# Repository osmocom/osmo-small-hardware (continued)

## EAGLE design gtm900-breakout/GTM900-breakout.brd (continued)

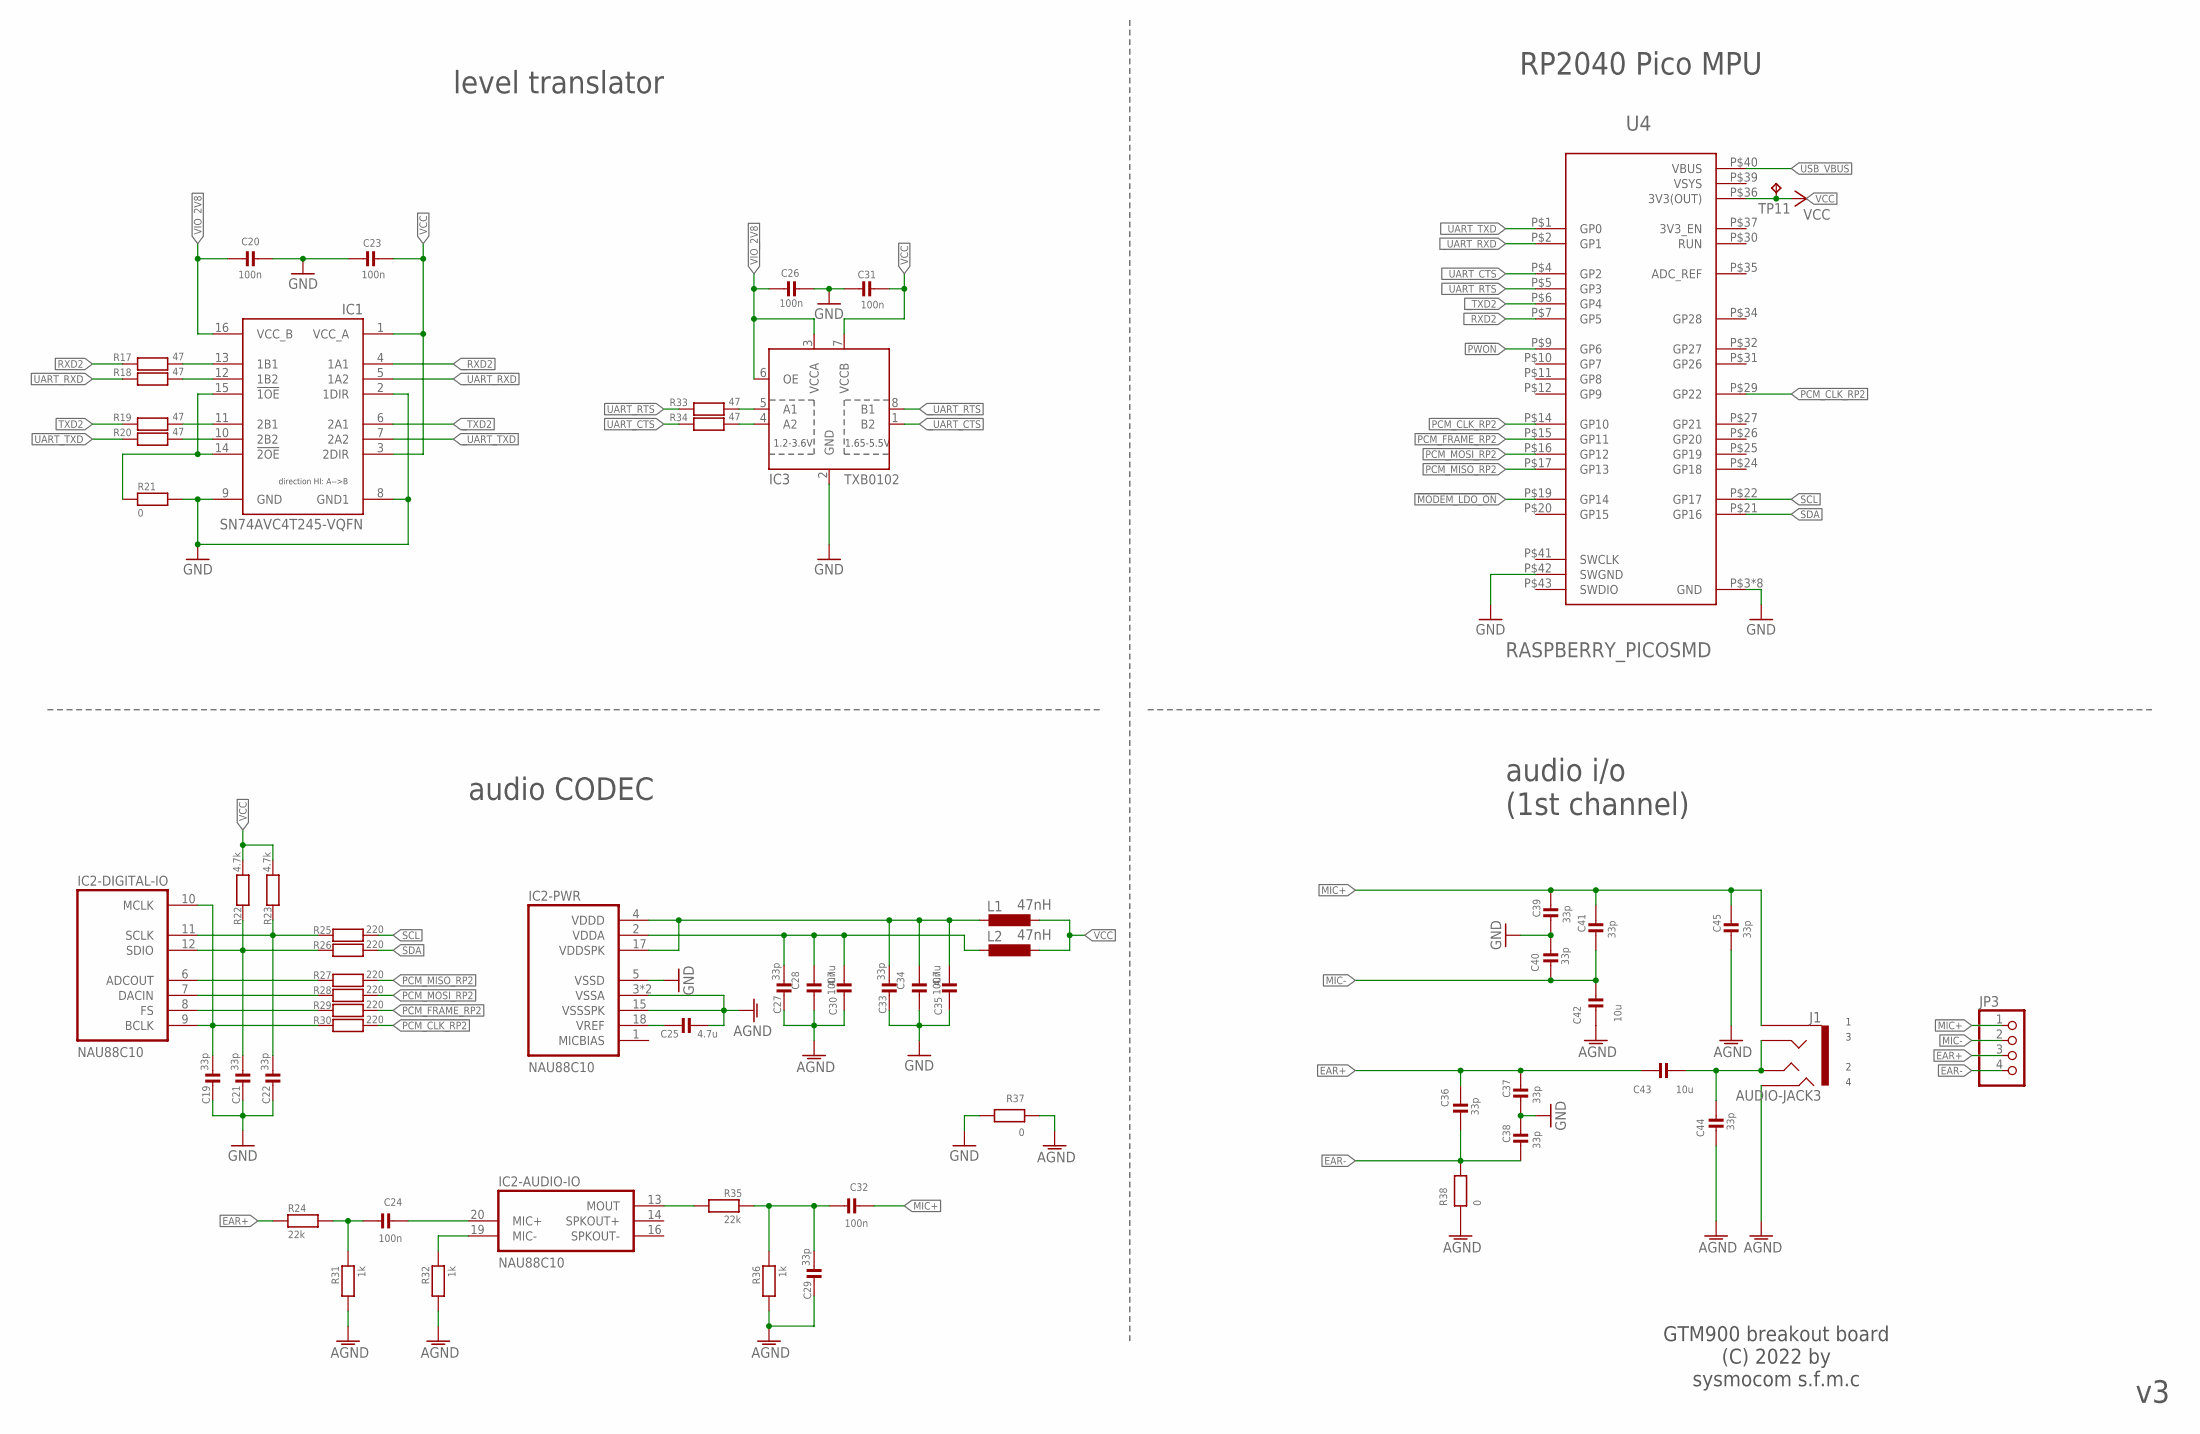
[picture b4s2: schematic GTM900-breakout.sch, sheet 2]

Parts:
C19, C21, C22, C27, C29, C33, C36, C37, C38, C39, C40, C41, C44, C45: 33p; _0402; MANUFACTURERPARTNUMBER CL05C330JB5NNNC; LCSC_PART C70465
C20, C23, C24, C26, C28, C31, C32, C34: 100n; _0603; MANUFACTURERPARTNUMBER CL10B104KB8NNWC; LCSC_PART C14663
C25, C30, C35: 4.7u; _0603; MANUFACTURERPARTNUMBER CC0603KRX5R6BB475; LCSC_PART C109456
C42, C43: 10u; _0805; MANUFACTURERPARTNUMBER GRM21BR61C106KE15K; LCSC_PART C408141
IC1: SN74AVC4T245-VQFN; VQFN-N16; MANUFACTURERPARTNUMBER SN74AVC4T245RGYR; LCSC_PART C2872438
IC2: NAU88C10; QFN20; MANUFACTURERPARTNUMBER NAU88C10YG; LCSC_PART C914208
IC3: TXB0102; VSSOP-8; MANUFACTURERPARTNUMBER TXB0102DCUR; LCSC_PART C60709
J1: AUDIO-JACK3; AUDIO-JACK-TRRS-SMD; MANUFACTURERPARTNUMBER SJ2-3574A-SMT-TR; LCSC_PART C4991637
JP3: HEADER-1X476MIL; 1X04_ROUND_76; MANUFACTURERPARTNUMBER UNKNOWN MANUFACTURER PART NUMBER; LCSC_PART UNKNOWN LCSC_PART
L1, L2: 47nH; _0603; MANUFACTURERPARTNUMBER BSCH0016080847NJ00; LCSC_PART C6135425
R17, R18, R19, R20, R33, R34: 47; _0603; MANUFACTURERPARTNUMBER RC0603JR-0747RL; LCSC_PART C114623
R21, R37, R38: 0; _0603; MANUFACTURERPARTNUMBER UNKNOWN MANUFACTURER PART NUMBER; LCSC_PART C136582
R22, R23: 4.7k; _0603; MANUFACTURERPARTNUMBER RC0603JR-074K7L; LCSC_PART C105428
R24, R35: 22k; _0603; MANUFACTURERPARTNUMBER RC0603FR-0722KL; LCSC_PART C114065
R25, R26, R27, R28, R29, R30: 220; _0603; MANUFACTURERPARTNUMBER RC0603FR-07220RL; LCSC_PART C107696
R31, R32, R36: 1k; _0603; MANUFACTURERPARTNUMBER RR0816P-102-D; LCSC_PART C116692
TP11: TPTP10R; TP10R; MANUFACTURERPARTNUMBER UNKNOWN MANUFACTURER PART NUMBER; LCSC_PART UNKNOWN LCSC_PART
U4: RASPBERRY_PICOSMD; PICO-PKG-SMD; MANUFACTURERPARTNUMBER SC0915; LCSC_PART UNKNOWN LCSC_PART

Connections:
!MODEM_LDO_ON: U4.P$19 (GP14); also elsewhere on the board
!PWON: U4.P$9 (GP6); also elsewhere on the board
AGND: C25.1, C27.2, C28.2, C29.2, C30.2, C42.2, C44.1, C45.2, IC2.3 (VSSA), IC2.15 (VSSSPK), IC2.EXP (VSSA), J1.4 (RING2), R31.2, R32.2, R36.2, R37.1, R38.1
EAR+: C36.2, C37.1, C43.2, JP3.3, R24.1; also elsewhere on the board
EAR-: C36.1, C38.2, JP3.4, R38.2; also elsewhere on the board
GND: C19.2, C20.2, C21.2, C22.2, C23.1, C26.2, C31.1, C33.2, C34.2, C35.2, C37.2, C38.1, C39.2, C40.2, IC1.2 (1DIR), IC1.8 (GND1), IC1.9 (GND), IC2.5 (VSSD), IC3.2 (GND), R21.2, R37.2, U4.P$3 (GND), U4.P$8 (GND), U4.P$13 (GND), U4.P$18 (GND), U4.P$23 (GND), U4.P$28 (GND), U4.P$33 (GND), U4.P$38 (GND), U4.P$42 (SWGND); also elsewhere on the board
MIC+: C32.1, C39.1, C41.1, C45.1, J1.1 (EARTH), JP3.1; also elsewhere on the board
MIC-: C40.1, C41.2, C42.1, JP3.2; also elsewhere on the board
MICBIAS: IC2.1 (MICBIAS)
unnamed: C24.2, R24.2, R31.1
unnamed: C43.1, C44.2, J1.2 (TIP), J1.3 (RING1)
unnamed: C19.1, IC2.9 (BCLK), IC2.10 (MCLK), R30.1
unnamed: IC2.8 (FS), R29.1
unnamed: IC2.7 (DACIN), R28.1
unnamed: IC2.6 (ADCOUT), R27.1
unnamed: C29.1, C32.2, R35.2, R36.1
unnamed: IC2.19 (MIC-), R32.1
unnamed: C33.1, C34.1, C35.1, IC2.4 (VDDD), IC2.17 (VDDSPK), L1.2
unnamed: IC1.14 (!2OE), IC1.15 (!1OE), R21.1
unnamed: IC1.13 (1B1), R17.1
unnamed: C27.1, C28.1, C30.1, IC2.2 (VDDA), L2.2
unnamed: C21.1, IC2.12 (SDIO), R22.1, R26.1
unnamed: C22.1, IC2.11 (SCLK), R23.1, R25.1
unnamed: IC1.12 (1B2), R18.1
unnamed: C25.2, IC2.18 (VREF)
unnamed: IC1.11 (2B1), R19.1
unnamed: IC2.13 (MOUT), R35.1
unnamed: C24.1, IC2.20 (MIC+)
unnamed: IC1.10 (2B2), R20.1
unnamed: IC3.5 (A1), R33.1
unnamed: IC3.4 (A2), R34.1
PCM_CLK_RP2: R30.2, U4.P$14 (GP10), U4.P$29 (GP22)
PCM_FRAME_RP2: R29.2, U4.P$15 (GP11)
PCM_MISO_RP2: R27.2, U4.P$17 (GP13)
PCM_MOSI_RP2: R28.2, U4.P$16 (GP12)
RXD2: R17.2; also elsewhere on the board
SCL: R25.2, U4.P$22 (GP17)
SDA: R26.2, U4.P$21 (GP16)
TXD2: R19.2; also elsewhere on the board
UART_CTS: R34.2; also elsewhere on the board
UART_RTS: R33.2; also elsewhere on the board
UART_RXD: R18.2; also elsewhere on the board
UART_TXD: R20.2; also elsewhere on the board
USB_VBUS: U4.P$40 (VBUS); also elsewhere on the board
VCC: C23.2, C31.2, IC1.1 (VCC_A), IC1.3 (2DIR), IC3.7 (VCCB), L1.1, L2.1, R22.2, R23.2, TP11.TP, U4.P$36 (3V3(OUT))
VIO_2V8: C20.1, C26.1, IC1.16 (VCC_B), IC3.3 (VCCA), IC3.6 (OE); also elsewhere on the board
VSYS: U4.P$39 (VSYS)
_RXD2: IC1.4 (1A1), U4.P$7 (GP5)
_TXD2: IC1.6 (2A1), U4.P$6 (GP4)
_UART_CTS: IC3.1 (B2), U4.P$4 (GP2)
_UART_RTS: IC3.8 (B1), U4.P$5 (GP3)
_UART_RXD: IC1.5 (1A2), U4.P$2 (GP1)
_UART_TXD: IC1.7 (2A2), U4.P$1 (GP0)

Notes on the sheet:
audio i/o (1st channel)
GTM900 breakout board (C) 2022 by sysmocom s.f.m.c
level translator
audio CODEC
RP2040 Pico MPU

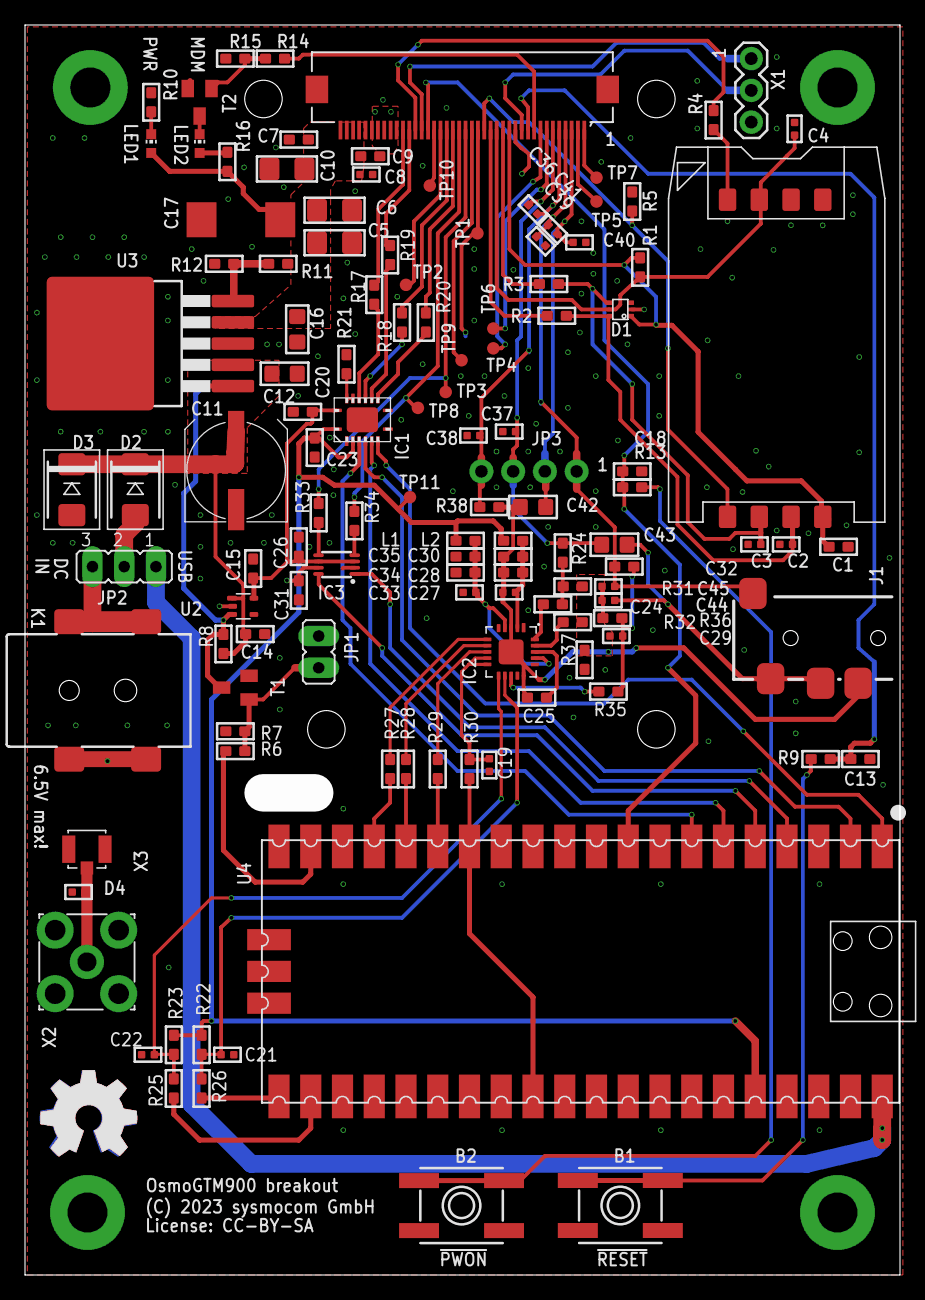
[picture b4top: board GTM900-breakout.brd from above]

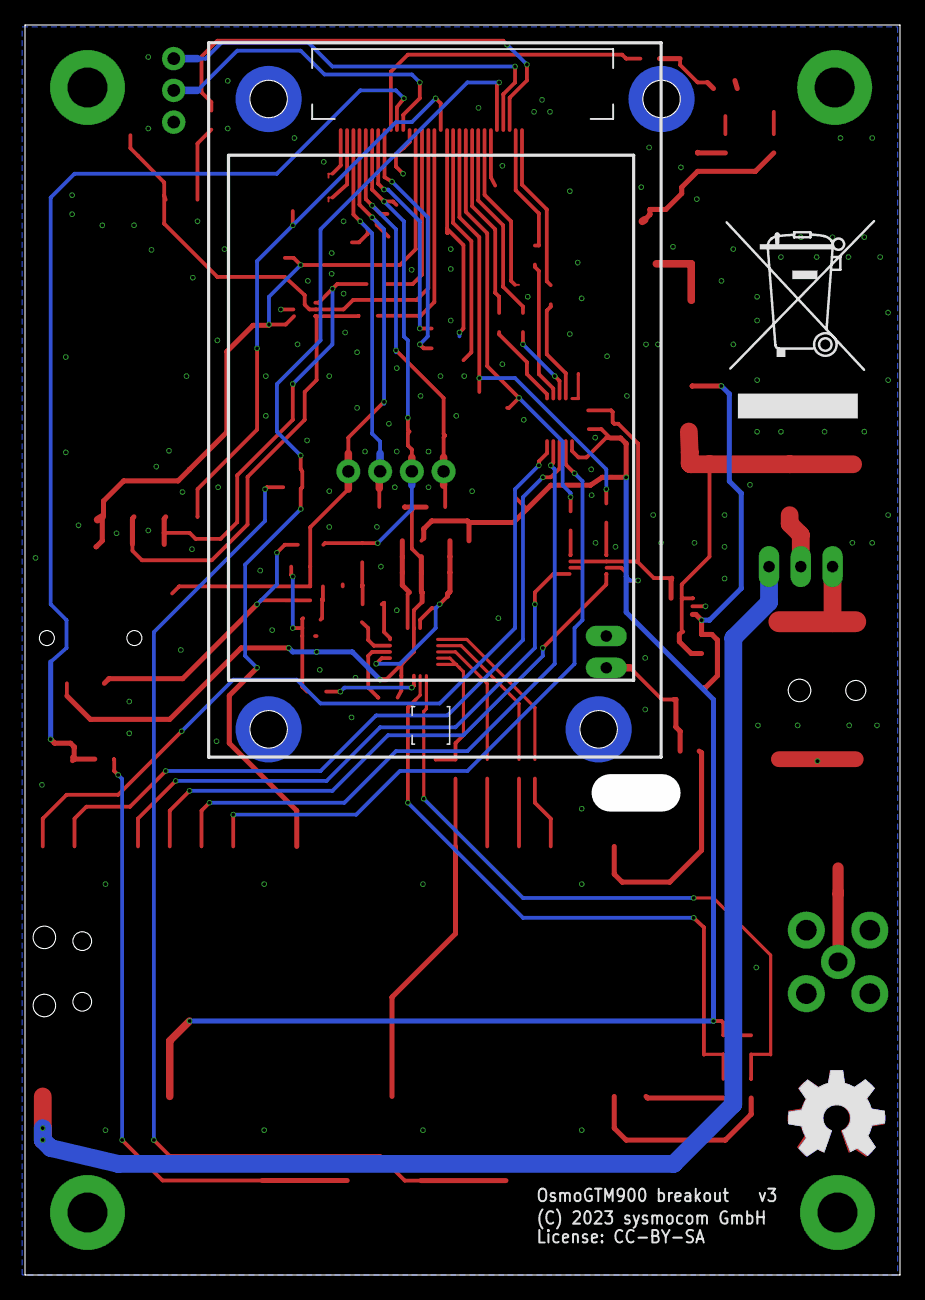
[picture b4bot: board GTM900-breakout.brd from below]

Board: 2 copper layers, 70.0 x 100.0 mm, 126 parts (3 on the bottom side), 86 nets.

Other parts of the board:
U$1, U$3: OSHW_8MM_COPPER
U$2: WEEE_BIN

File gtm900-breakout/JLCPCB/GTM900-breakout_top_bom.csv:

Comment,Designator,Footprint,"LCSC Part #"
uFL,X3,HRS_UFL,C434812
"0R jumper","R21 R37 R38",_0603,C136582
1k,"R9 R13 R31 R32 R36",_0603,C116692
1u,"C14 C15",_0603,C1592
4.7k,"R4 R8 R22 R23",_0603,C105428
4.7u,"C25 C30 C35",_0603,C109456
10p,C9,_0603,C106245
10u,"C12 C16 C42 C43",_0805,C408141
15k,R1,_0603,C114661
22k,"R6 R7 R12 R14 R15 R24 R35",_0603,C114065
33p,"C2 C3 C4 C8 C19 C21 C22 C27 C29 C33 C36 C37 C38 C39 C40 C41 C44 C45",_0402,C70465
47R,"R2 R3 R17 R18 R19 R20 R33 R34",_0603,C114623
47k,R5,_0603,C105579
47nH,"L1 L2",_0603,C6135425
100n,"C1 C7 C13 C18 C20 C23 C24 C26 C28 C31 C32 C34",_0603,C141084
100u,"C5 C6 C10",1206,C15008
200k,R11,_0603,C105574
220R,"R25 R26 R27 R28 R29 R30",_0603,C107696
330R,"R10 R16",_0603,C105879
470u,C11,UD-8X10_NICHICON,C445244
ACDBB540-HF,D2,SMBDIODE,C3019736
AUDIO-JACK3,J1,AUDIO-JACK-TRRS-SMD,C4991637
BC847,"T1 T2",SOT23-BEC,C8664
EVQQ2K03W,"B1 B2",EVQ-Q2,C713484
FH12A-40S-0.5SH(55),U1,HIROSE_FH12A-40S-0.5SH(55),C506795
GG040205170N2P,D4,_0402,C597648
GREEN,LED1,CHIP-LED0603,C5554150
MCP1827T-ADJE/ET,U3,TI_KTT_DPAK2,C152196
MIC5366,U2,SC70-5,C626107
NAU88C10,IC2,QFN20,C914208
PESD5V0UBV,D1,SOT666,C552582
PJ-002BH-SMT-TR,K1,694108106102,C3094235
SIM-105B-ARP8,SIM1,SIM-105B-ARP8,C920196
SMBJP6KE6.8A-TP,D3,SMBDIODE,C725414
SN74AVC4T245-VQFN,IC1,VQFN-N16,C2872438
TXB0102,IC3,VSSOP-8,C60709
YELLOW,LED2,CHIP-LED0603,C5875726

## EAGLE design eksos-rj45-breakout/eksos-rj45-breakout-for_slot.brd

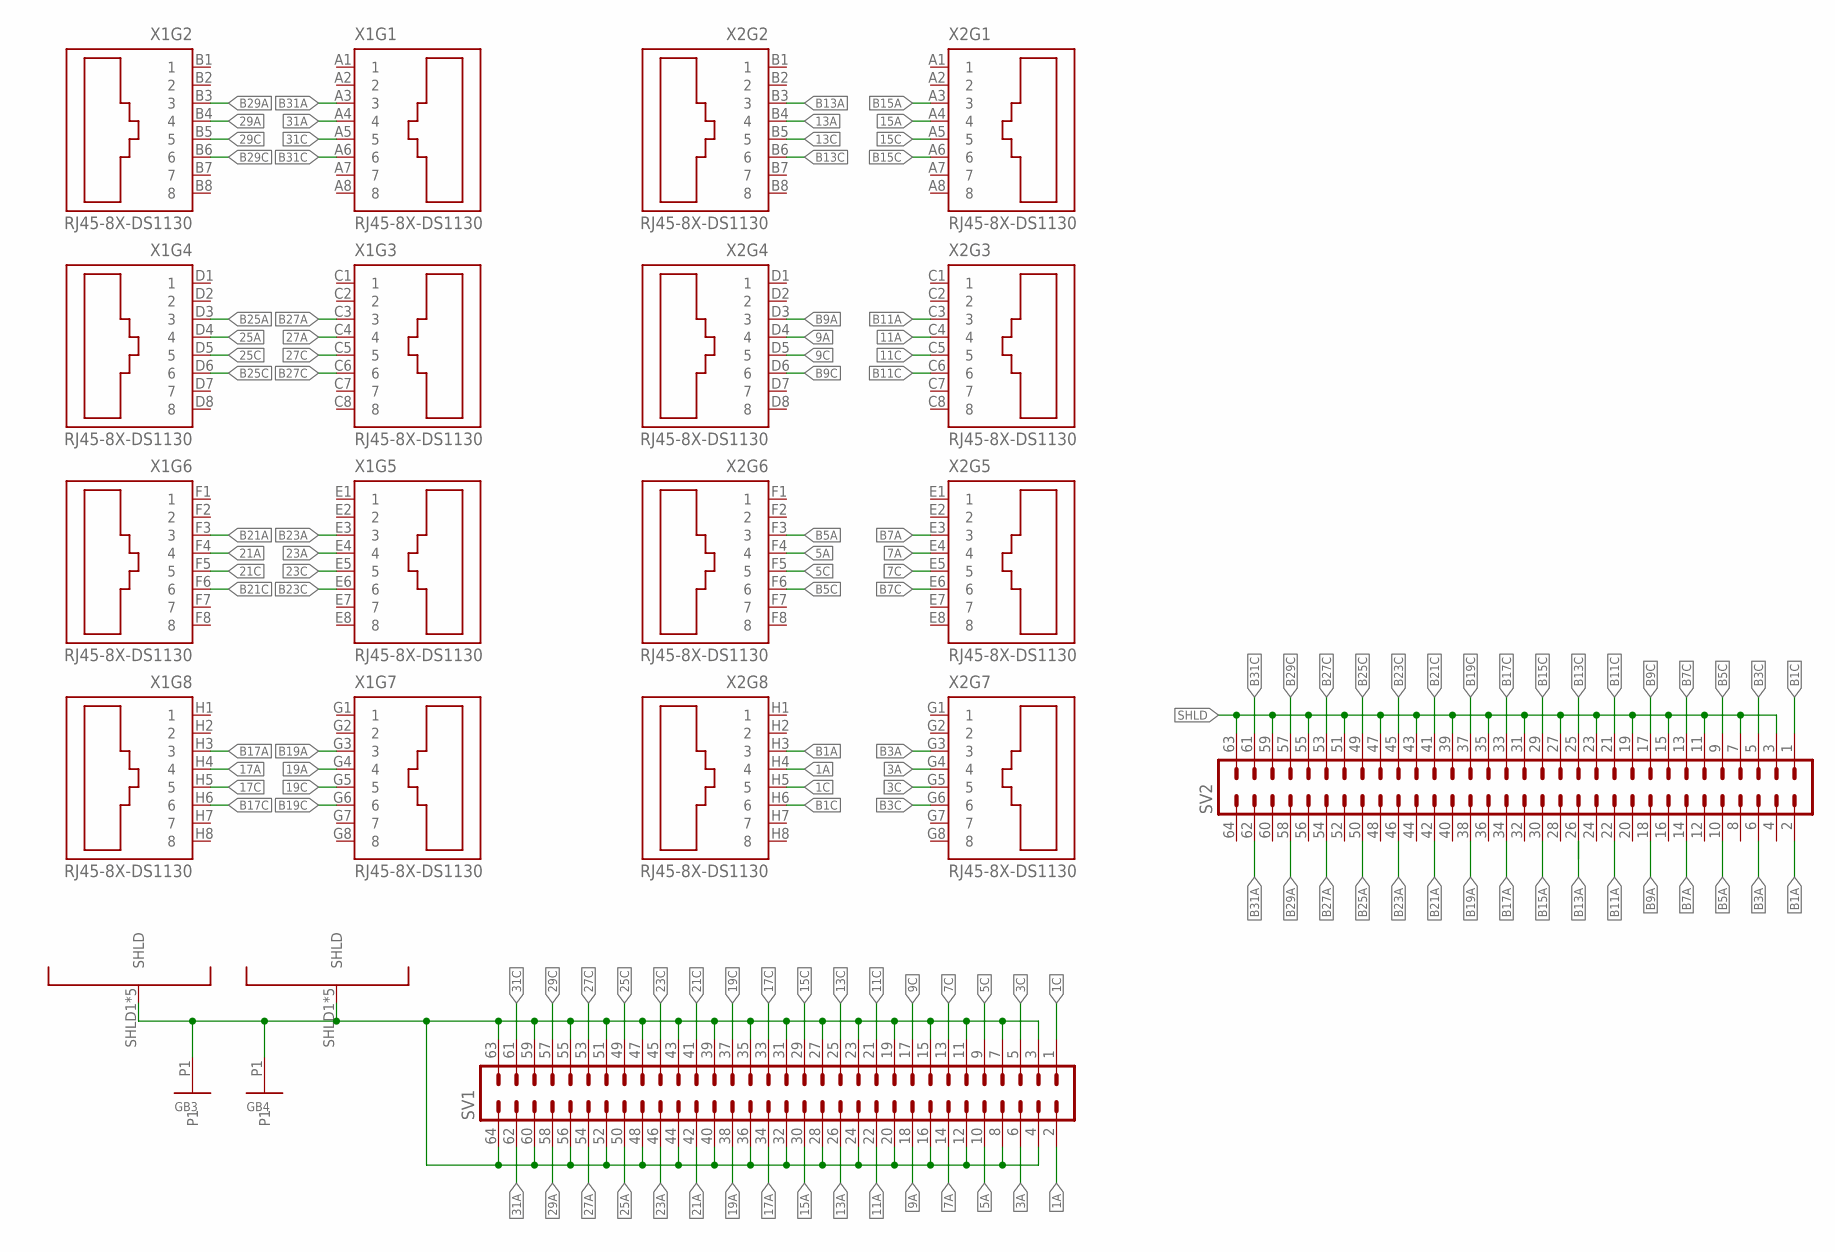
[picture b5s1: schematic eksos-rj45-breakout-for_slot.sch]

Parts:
GB3, GB4: GEWINDEBLOCK-6X6X12M3; GB6X6X12_VIA
SV1, SV2: ML64
X1, X2: RJ45-8X-DS1130; DS1130

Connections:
1A: SV1.2, X2.H4 (4)
1C: SV1.1, X2.H5 (5)
3A: SV1.6, X2.G4 (4)
3C: SV1.5, X2.G5 (5)
5A: SV1.10, X2.F4 (4)
5C: SV1.9, X2.F5 (5)
7A: SV1.14, X2.E4 (4)
7C: SV1.13, X2.E5 (5)
9A: SV1.18, X2.D4 (4)
9C: SV1.17, X2.D5 (5)
11A: SV1.22, X2.C4 (4)
11C: SV1.21, X2.C5 (5)
13A: SV1.26, X2.B4 (4)
13C: SV1.25, X2.B5 (5)
15A: SV1.30, X2.A4 (4)
15C: SV1.29, X2.A5 (5)
17A: SV1.34, X1.H4 (4)
17C: SV1.33, X1.H5 (5)
19A: SV1.38, X1.G4 (4)
19C: SV1.37, X1.G5 (5)
21A: SV1.42, X1.F4 (4)
21C: SV1.41, X1.F5 (5)
23A: SV1.46, X1.E4 (4)
23C: SV1.45, X1.E5 (5)
25A: SV1.50, X1.D4 (4)
25C: SV1.49, X1.D5 (5)
27A: SV1.54, X1.C4 (4)
27C: SV1.53, X1.C5 (5)
29A: SV1.58, X1.B4 (4)
29C: SV1.57, X1.B5 (5)
31A: SV1.62, X1.A4 (4)
31C: SV1.61, X1.A5 (5)
B1A: SV2.2, X2.H3 (3)
B1C: SV2.1, X2.H6 (6)
B3A: SV2.6, X2.G3 (3)
B3C: SV2.5, X2.G6 (6)
B5A: SV2.10, X2.F3 (3)
B5C: SV2.9, X2.F6 (6)
B7A: SV2.14, X2.E3 (3)
B7C: SV2.13, X2.E6 (6)
B9A: SV2.18, X2.D3 (3)
B9C: SV2.17, X2.D6 (6)
B11A: SV2.22, X2.C3 (3)
B11C: SV2.21, X2.C6 (6)
B13A: SV2.26, X2.B3 (3)
B13C: SV2.25, X2.B6 (6)
B15A: SV2.30, X2.A3 (3)
B15C: SV2.29, X2.A6 (6)
B17A: SV2.34, X1.H3 (3)
B17C: SV2.33, X1.H6 (6)
B19A: SV2.38, X1.G3 (3)
B19C: SV2.37, X1.G6 (6)
B21A: SV2.42, X1.F3 (3)
B21C: SV2.41, X1.F6 (6)
B23A: SV2.46, X1.E3 (3)
B23C: SV2.45, X1.E6 (6)
B25A: SV2.50, X1.D3 (3)
B25C: SV2.49, X1.D6 (6)
B27A: SV2.54, X1.C3 (3)
B27C: SV2.53, X1.C6 (6)
B29A: SV2.58, X1.B3 (3)
B29C: SV2.57, X1.B6 (6)
B31A: SV2.62, X1.A3 (3)
B31C: SV2.61, X1.A6 (6)
SHLD: GB3.P1, GB4.P1, SV1.3, SV1.4, SV1.7, SV1.8, SV1.11, SV1.12, SV1.15, SV1.16, SV1.19, SV1.20, SV1.23, SV1.24, SV1.27, SV1.28, SV1.31, SV1.32, SV1.35, SV1.36, SV1.39, SV1.40, SV1.43, SV1.44, SV1.47, SV1.48, SV1.51, SV1.52, SV1.55, SV1.56, SV1.59, SV1.60, SV1.63, SV1.64, SV2.3, SV2.7, SV2.11, SV2.15, SV2.19, SV2.23, SV2.27, SV2.31, SV2.35, SV2.39, SV2.43, SV2.47, SV2.51, SV2.55, SV2.59, SV2.63, X1.SHLD1 (SHLD), X1.SHLD2 (SHLD), X1.SHLD3 (SHLD), X1.SHLD4 (SHLD), X1.SHLD5 (SHLD), X2.SHLD1 (SHLD), X2.SHLD2 (SHLD), X2.SHLD3 (SHLD), X2.SHLD4 (SHLD), X2.SHLD5 (SHLD)

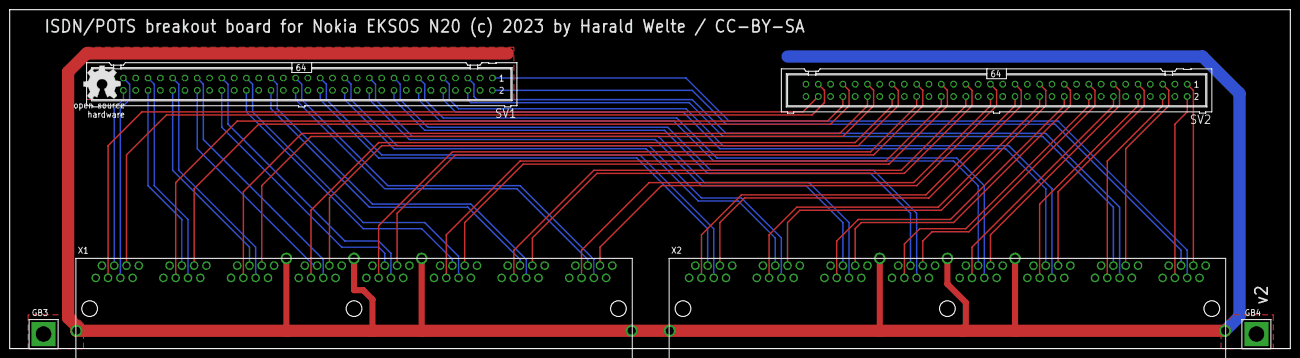
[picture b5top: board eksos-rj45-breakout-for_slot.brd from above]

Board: 2 copper layers, 264.5 x 70.0 mm, 7 parts (0 on the bottom side), 65 nets.

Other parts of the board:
U$1: OSHW_8MM

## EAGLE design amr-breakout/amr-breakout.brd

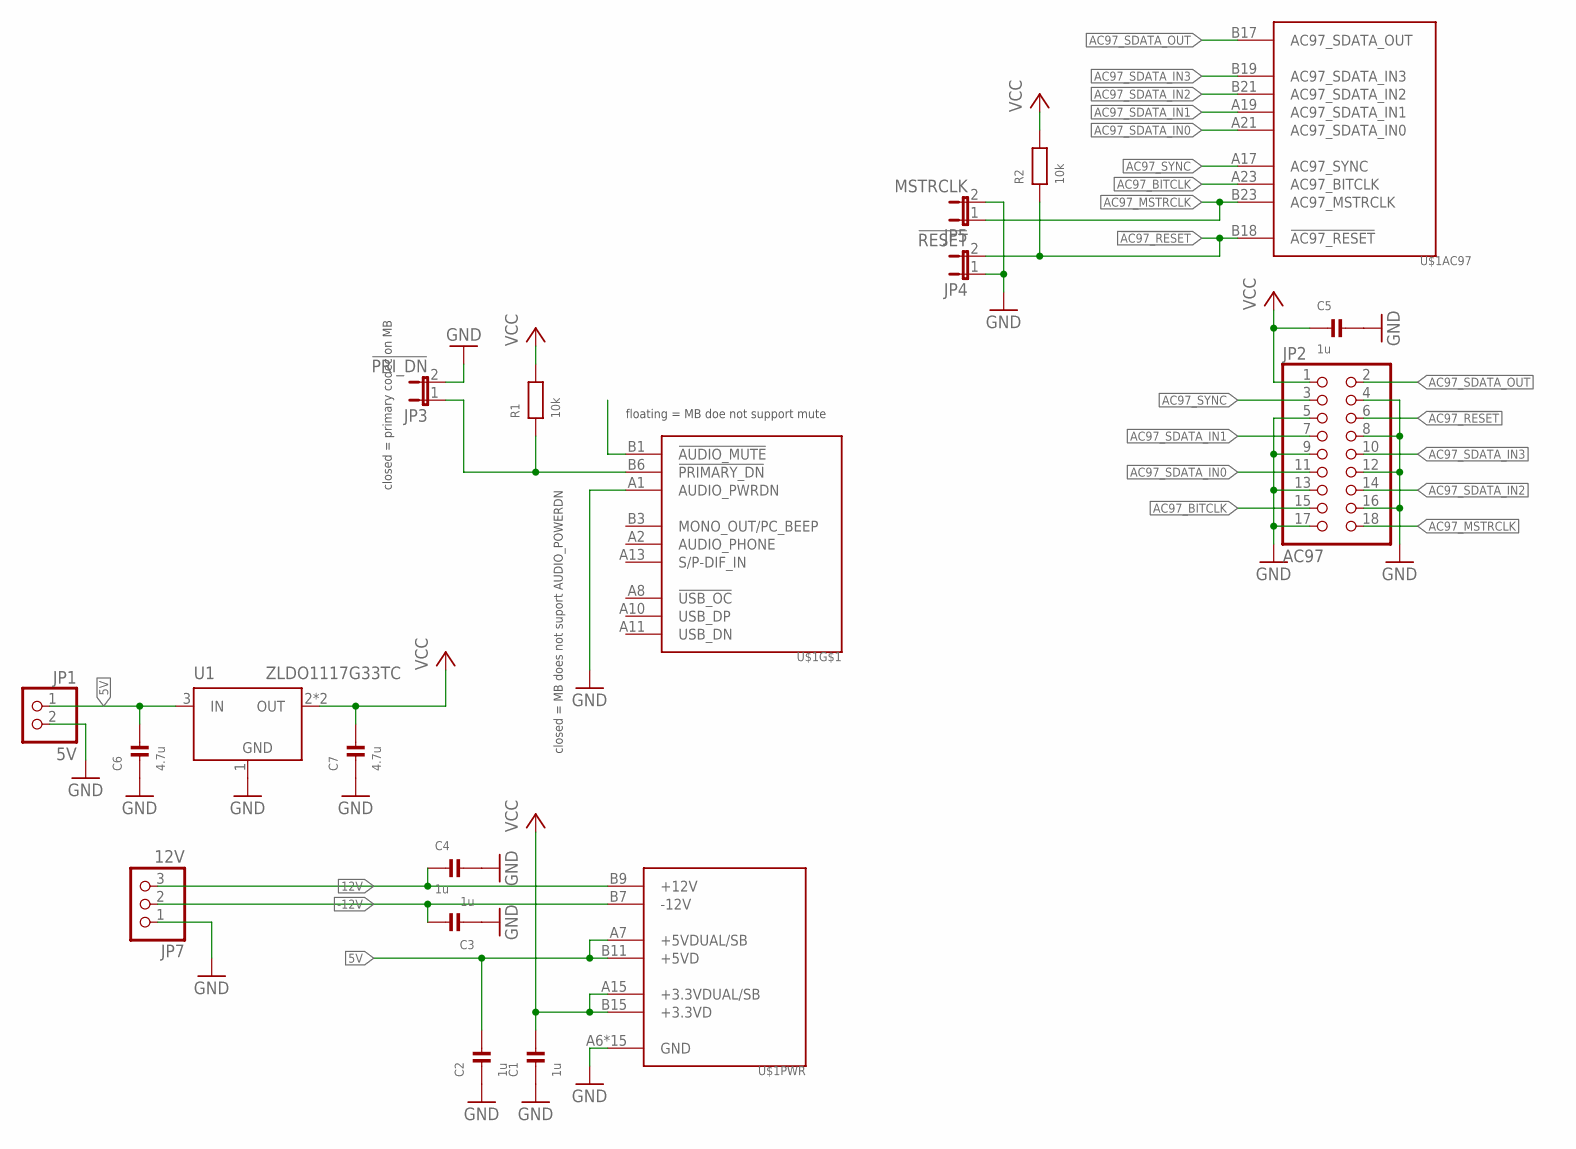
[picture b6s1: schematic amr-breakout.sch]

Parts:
C1, C2, C3, C4, C5: 1u; _0603
C6, C7: 4.7u; _0805
JP1: 5V; 1X02
JP2: AC97; 2X09
JP3: !PRI_DN; JP1
JP4: !RESET; JP1
JP5: MSTRCLK; JP1
JP7: 12V; 1X03
R1, R2: 10k; _0603
U1: ZLDO1117G33TC; SOT223
U$1: AMR-SLOT; 5650090-7

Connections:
5V: C2.2, C6.2, JP1.1, U1.3 (IN), U$1.A7 (+5VDUAL/SB), U$1.B11 (+5VD)
12V: C4.1, JP7.3, U$1.B9 (+12V)
!AC97_RESET: JP2.6, JP4.2, R2.1, U$1.B18 (!AC97_RESET)
!AUDIO_MUTE: U$1.B1 (!AUDIO_MUTE)
!PRIMARY_DN: JP3.1, R1.1, U$1.B6 (!PRIMARY_DN)
-12V: C3.2, JP7.2, U$1.B7 (-12V)
AC97_BITCLK: JP2.15, U$1.A23 (AC97_BITCLK)
AC97_MSTRCLK: JP2.18, JP5.1, U$1.B23 (AC97_MSTRCLK)
AC97_SDATA_IN0: JP2.11, U$1.A21 (AC97_SDATA_IN0)
AC97_SDATA_IN1: JP2.7, U$1.A19 (AC97_SDATA_IN1)
AC97_SDATA_IN2: JP2.14, U$1.B21 (AC97_SDATA_IN2)
AC97_SDATA_IN3: JP2.10, U$1.B19 (AC97_SDATA_IN3)
AC97_SDATA_OUT: JP2.2, U$1.B17 (AC97_SDATA_OUT)
AC97_SYNC: JP2.3, U$1.A17 (AC97_SYNC)
GND: C1.1, C2.1, C3.1, C4.2, C5.2, C6.1, C7.1, JP1.2, JP2.4, JP2.5, JP2.8, JP2.9, JP2.12, JP2.13, JP2.16, JP2.17, JP3.2, JP4.1, JP5.2, JP7.1, U1.1 (GND), U$1.A1 (AUDIO_PWRDN), U$1.A6 (GND), U$1.A9 (GND), U$1.A12 (GND), U$1.A14 (GND), U$1.A16 (GND), U$1.A18 (GND), U$1.A20 (GND), U$1.A22 (GND), U$1.B2 (GND), U$1.B8 (GND), U$1.B10 (GND), U$1.B12 (GND), U$1.B16 (GND), U$1.B20 (GND), U$1.B22 (GND)
VCC: C1.2, C5.1, C7.2, JP2.1, R1.2, R2.2, U1.2 (OUT), U1.4 (OUT), U$1.A15 (+3.3VDUAL/SB), U$1.B15 (+3.3VD)

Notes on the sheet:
closed = MB does not suport AUDIO_POWERDN
floating = MB doe not support mute
closed = primary codec on MB

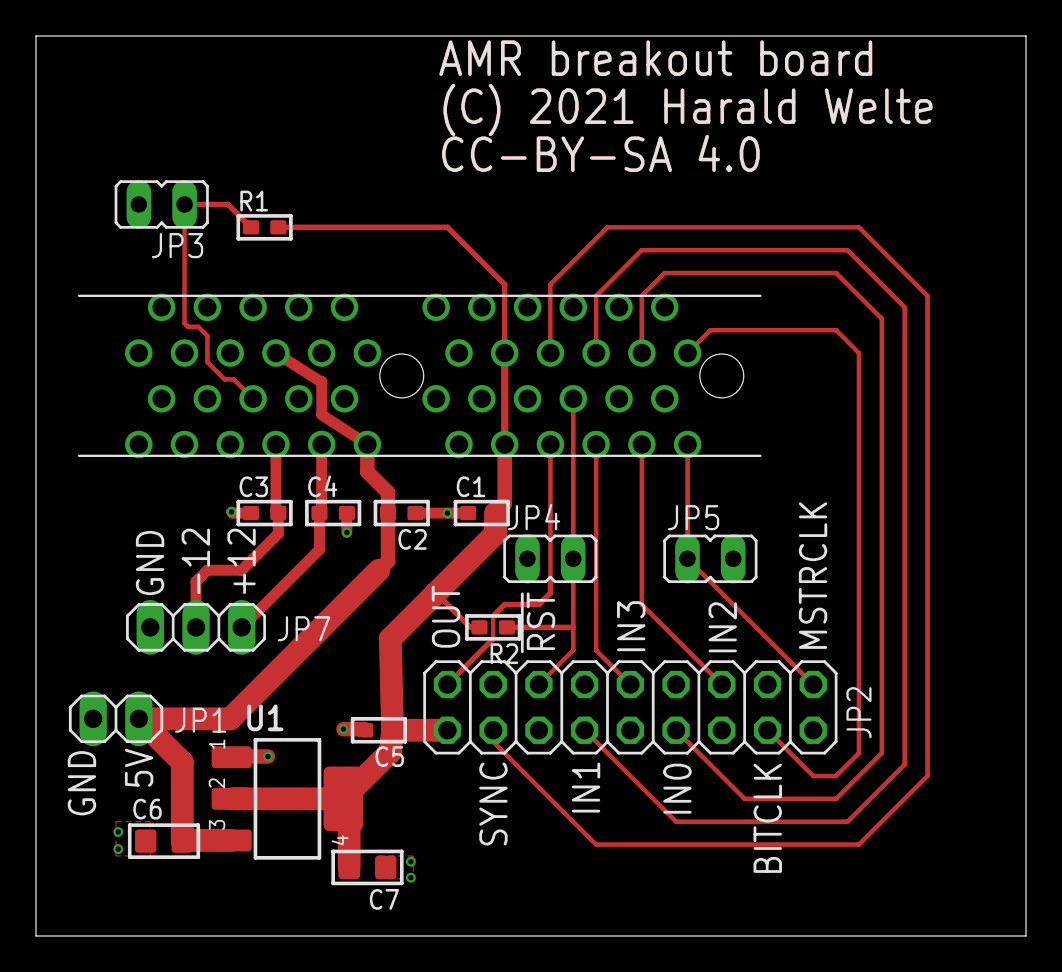
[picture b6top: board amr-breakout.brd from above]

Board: 2 copper layers, 55.0 x 50.0 mm, 17 parts (0 on the bottom side), 15 nets.

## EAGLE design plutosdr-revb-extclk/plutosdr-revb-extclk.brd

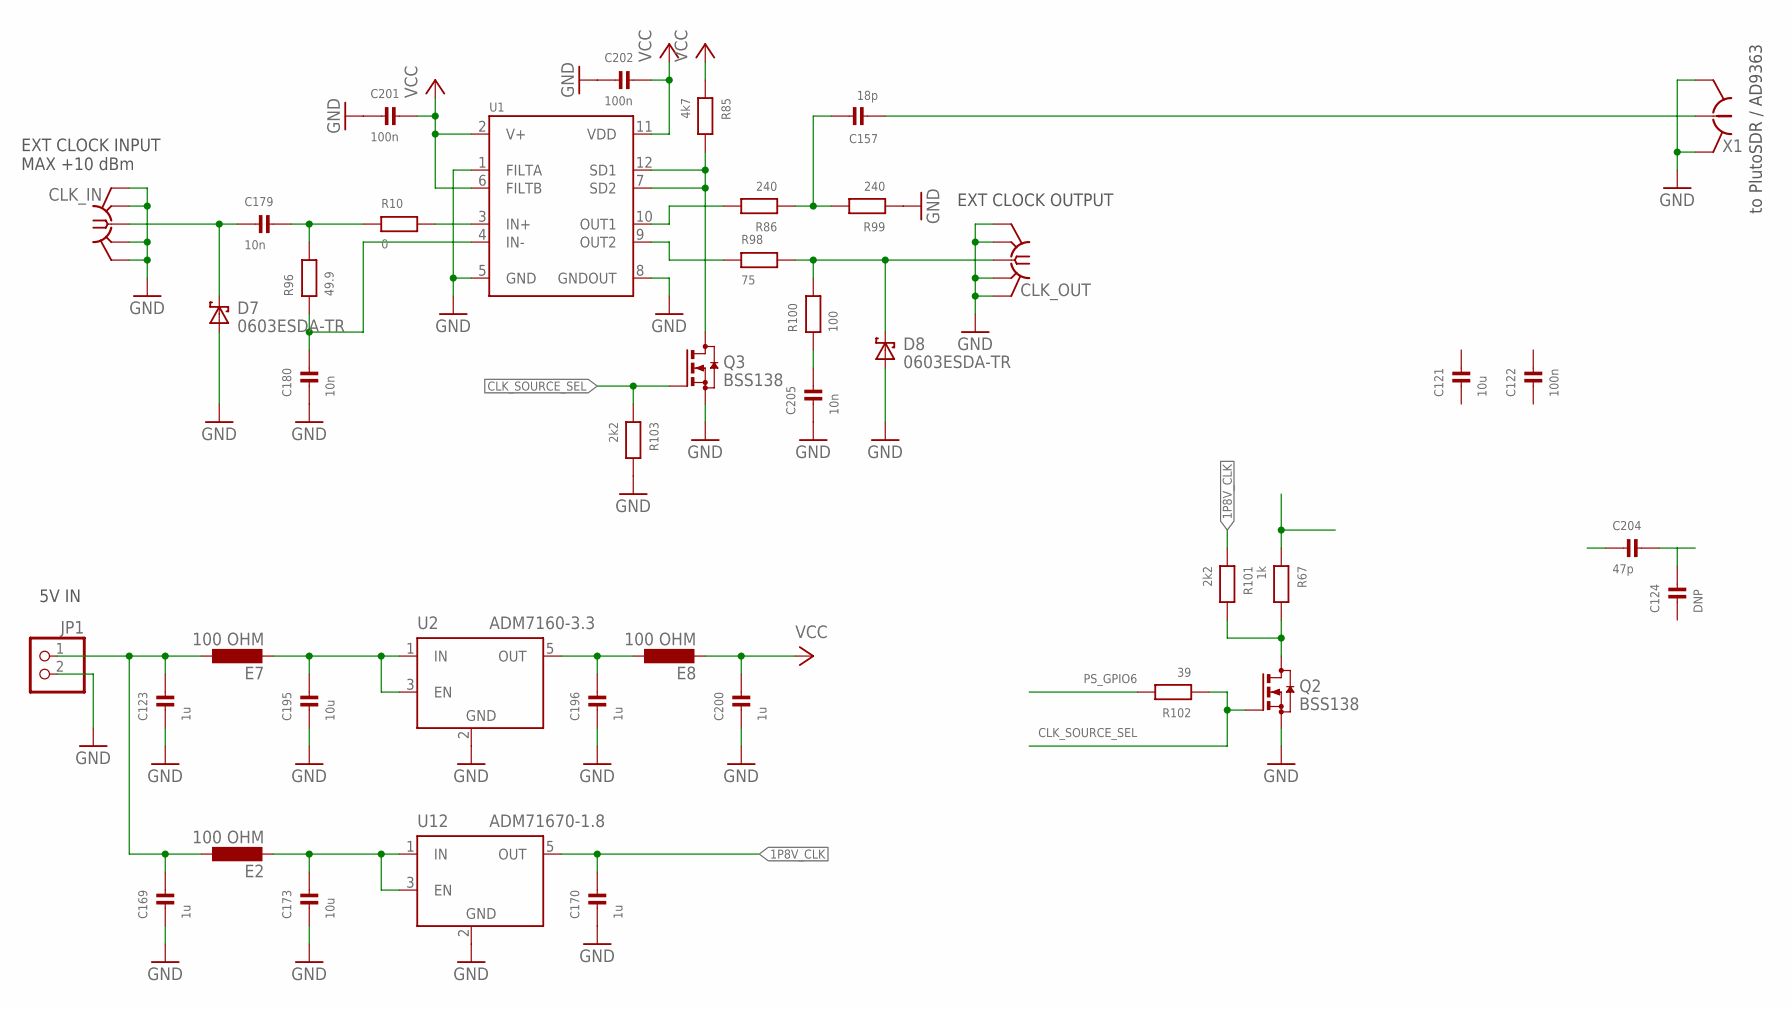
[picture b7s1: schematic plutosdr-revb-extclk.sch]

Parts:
C121, C173, C195: 10u; _0805
C122, C201, C202: 100n; _0603
C123, C169, C170, C196, C200: 1u; _0603
C124: DNP; _0603
C157: 18p; _0603
C179, C180, C205: 10n; _0603
C204: 47p; _0603
CLK_IN: SMA-F73251-2201; SMA-F-S-TH-73251-2201
CLK_OUT: SMA-F73251-2201; SMA-F-S-TH-73251-2201
D7, D8: 0603ESDA-TR; 0603
E2, E7, E8: 100 OHM; 0805
JP1: PINHD-1X2/90; 1X02/90
Q2, Q3: BSS138; SOT23
R10: 0; _0603
R67: 1k; _0603
R85: 4k7; _0603
R86, R99: 240; _0603
R96: 49.9; _0603
R98: 75; _0603
R100: 100; _0603
R101, R103: 2k2; _0603
R102: 39; _0603
U1: LTC6957-3/4-HMS; MSOP12
U2: ADM7160-3.3; SOT23L
U12: ADM71670-1.8; SOT23L
X1: HRS_UFL

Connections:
1P8V_CLK: C170.2, R101.1, U12.5 (OUT)
3V3_OUT: C196.2, E8.1, U2.5 (OUT)
5V_FILTERED: C195.2, E7.2, U2.1 (IN), U2.3 (EN)
5V_IN: C123.2, C169.2, E2.1, E7.1, JP1.1
CLK_SOURCE_SEL: Q2.1 (G), Q3.1 (G), R102.1, R103.1
GND: C123.1, C169.1, C170.1, C173.1, C180.1, C195.1, C196.1, C200.1, C201.1, C202.1, C205.1, CLK_IN.G1 (GND), CLK_IN.G2 (GND), CLK_IN.G3 (GND), CLK_IN.G4 (GND), CLK_OUT.G1 (GND), CLK_OUT.G2 (GND), CLK_OUT.G3 (GND), CLK_OUT.G4 (GND), D7.1 (A), D8.1 (A), JP1.2, Q2.2 (S), Q3.2 (S), R99.1, R103.2, U1.1 (FILTA), U1.5 (GND), U1.8 (GNDOUT), U2.2 (GND), U12.2 (GND), X1.GND@1 (GND), X1.GND@2 (GND)
unnamed: C157.2, R86.1, R99.2
unnamed: R86.2, U1.10 (OUT1)
unnamed: R10.2, U1.3 (IN+)
unnamed: C180.2, R96.1, U1.4 (IN-)
unnamed: C179.2, R10.1, R96.2
unnamed: R98.1, U1.9 (OUT2)
unnamed: Q3.3 (D), R85.2, U1.7 (SD2), U1.12 (SD1)
unnamed: CLK_OUT.C (1), D8.2 (K), R98.2, R100.2
unnamed: C205.2, R100.1
unnamed: C179.1, CLK_IN.C (1), D7.2 (K)
unnamed: C173.2, E2.2, U12.1 (IN), U12.3 (EN)
unnamed: Q2.3 (D), R67.2, R101.2
unnamed: C124.2, C204.2
unnamed: C157.1, X1.SIG (1)
PS_GPIO6: R102.2
VCC: C200.2, C201.2, C202.2, E8.2, R85.1, U1.2 (V+), U1.6 (FILTB), U1.11 (VDD)

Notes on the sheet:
to PlutoSDR / AD9363
EXT CLOCK INPUT MAX +10 dBm
EXT CLOCK OUTPUT
5V IN

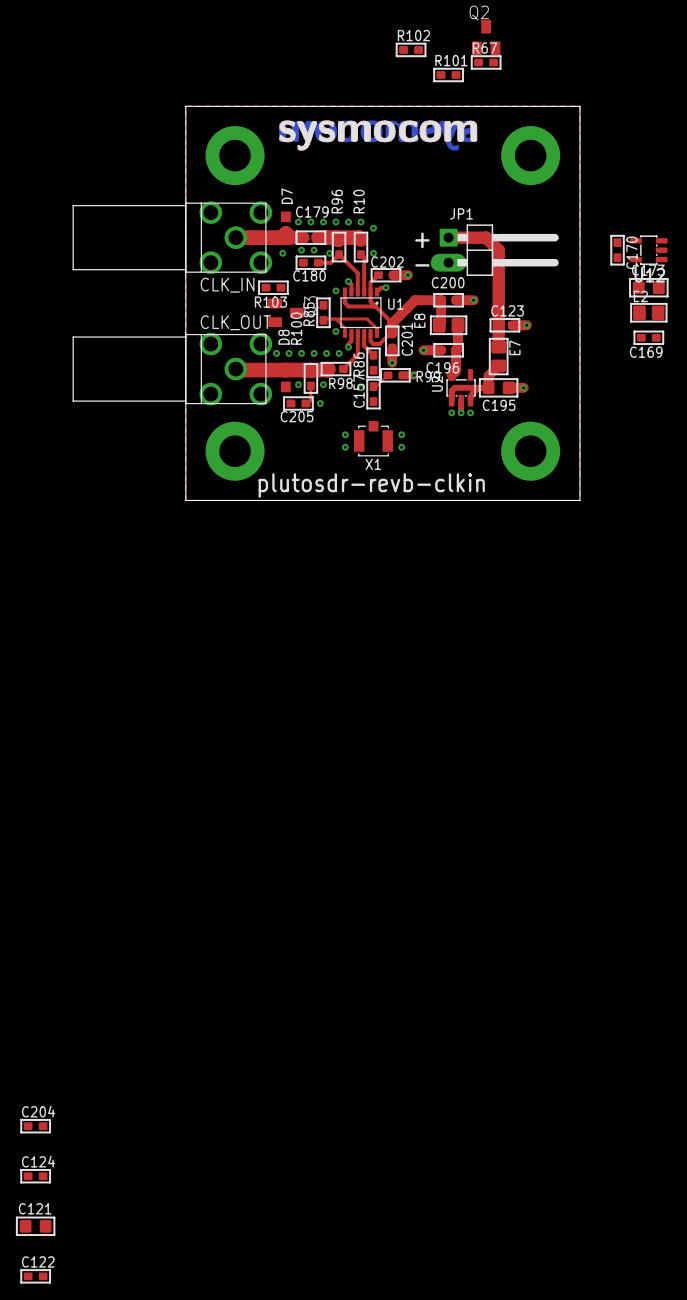
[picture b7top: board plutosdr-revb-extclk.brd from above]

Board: 2 copper layers, 40.0 x 40.0 mm, 46 parts (0 on the bottom side), 21 nets.

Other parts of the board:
U$1: SYSMOCOM-20-TOP
U$2: SYSMOCOM-20
U$3: SYSMOCOM-20-BOT
U$4: SYSMOCOM-20-BPLACE
